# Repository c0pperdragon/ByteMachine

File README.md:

# ByteMachine

Building an 8-bit computer is not exactly trivial. There are always many components involved which are normally
connected to some common address and data bus with complex control signal timings for RAM, ROM and IO controller parts and
whatnot.

One common way for a hobbyist user to actually build such a contraption is using a pre-engineered PCB on which to 
solder all necessary parts. While this can be great fun in itself, it does not teach you much about the hardware 
beyond basic soldering skills. 

Another way is creating the whole computer totally on breadboards. There are great resources and instructions available for
this and it may actually give you the best learning experience. On the other hand, creating a huge breadboard circuit comes with
its own troubles. The cables will often become a total mess, you easily disturb the wrong wires while changing anything, some wires
may make bad contact and you may not get the machine to run at a higher system clock.

With this design as a building block, I wanted to provide some kind of middle ground. The PCB provides the circuity for the system bus, RAM, ROM, clock, powerup reset 
and rudimentary IO. You then need to add a relatively small circuit for the CPU board, depending on the type of CPU to use. This can
be easily done with a single breadboard and a series of jumper links connecting this with the main board. In my experients this creates a 
pretty reliable setup which is even able to use clock frequencies of up to 16Mhz (for the 65Cxx types of CPUs).
Currently I have built and tested setups for the following CPUs:
* [65C02](65c02)
* [65C816](65c816)
* [Z84C00](z84c00)
* [i8088](i8088)

User [oe7twj](https://github.com/oe7twj) has provided me with all documention for this own setup:
* [6809](6809)

## CPU board connector

The main board has a 34 pin single-row connector that carries power and all signals necessary for the CPU to send and receive:
* Power connectors GND and +5V
* CPU Clock 
* Reset (active low)
* WR (active low)
* RD (active low)
* ROM selector 
* 19 Address bus lines
* 8 Data bus lines (bidirectional)

## Clock generator

The main board provides a simple circuit to create a clock signal using a quartz crystal. The quartz itself is socketed, so
you can easily exchange it to experiment with different frequencies. In my tests, this circuit runs reliably with frequencies
from 8Mhz up to 20Mhz (but this may be too fast for your CPU).

## Power-on reset

Most (probably all) supported CPUs need some external help to cleanly start upon power-up. The power-up reset line provides a
low level signal for the first few milliseconds after power is available. 

## Reading and writing strobes

Beyond providing the CPU clock, the main board itself does not use this clock for anything itself, and all accesses to
both RAM, ROM and IO are triggered by asynchronous signals. 

When the CPU needs to do a read, it sets up the address lines as 
well as the ROM selector and then pulls the RD line low. As long as this is in its low state, the board will provide
the requested data on the data bus. It is in the responsibility of the CPU to never drive the data bus itself as long as
the RD line is low.

For writing data to the board, the CPU needs to provide both the address (and ROM selector) and the data on the data bus.
Then it needs to pull WR low and set it high again (after some minimum setup-time). The data that is present at the rising 
edge will be written to the RAM (or IO).

## ROM, RAM, IO

The main board contains 512K of RAM, 512K of ROM (actually a NAND-Flash IC in a ZIF socket for ease of re-programming)
and two 74-series logic ICs to drive the input and output interface.

Contrary to most 8-bit computer designs, there is no dedicated address space to access IO (memory mapped IO) as this would
require some complex address decoding logic. Also a dedicated IO space would reduce the address space available, and for 
a CPU with only 16 address lines total, this is a serious drawback.

In my solution, the only IO the CPU can do is to write into an 8-bit output port register and to read 8 bits from an input 
port. Writing to the output is simply done by writing anywhere to the ROM address range. The data byte written will be stored
in the output register and will show up as voltages on the output port and will also directly drive the output LEDs.
To also allow input with as little logic parts as possible, I chose the following mechanism: 
After a write to the ROM area (and in consequence to the output port as well), the main board switches to "IO mode".
In IO mode, all reads from the RAM area will instead read data form the input port. 
To switch back to normal mode, the CPU needs to do a write to any RAM address. 
Using this scheme, the full range of ROM and RAM is available, as well as 8 output lines and 8 input lines.

## Attaching IO 

With a total of 8 output lines and 8 input lines (each with 10K pullups), basically any kind of serial IO protocol can be implemented
by the CPU: SPI, I2C, UART.

To keep things simple, the ByteBoard does not directly support any kind of IO interrupt line. Therefore basically only IO 
schemes are possible where the CPU is the master of the timing. This is already an inherent characteristic of the I2C and SPI
bus. To implement reliable UART communication, the connected device must support hardware flow control (RTS/CTS) at least 
on the incomming signal, so the CPU needs only to listen for data when it is itself prepared for that.

## Bidirectional lines for I2C 

To form the bi-directional line that is needed for I2C, one output and one input line can be combined.
The output pin can for example drive an open-collector circuit (an IC or only a simple transistor circuit). An even 
simpler possibility is just a diode that pulls down the line when the output pin is driven low, but lets the line
float when the pin is driven high. Due to the pullup resitors already present at the input port pins, this is
basically all that is needed.

## Reprogamming the Flash

From the perspective of the ByteMachine, its ROM is truly read-only. So you need an external programming device
to get new content onto the NAND-Flash. I am using an TL866II+ device which works absolutely fine for me. But 
any other compatible programmer will work, and you can even create an Arduino-Based circuit for that.

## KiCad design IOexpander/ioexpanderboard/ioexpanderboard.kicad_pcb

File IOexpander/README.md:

# IO expander

To allow more sophisticated communication with the outside world than just blinking lights and buttons, 
a small IO board can be attached to the headers of the IO area. This boards provides two serial communication
ports and one SDcard socket.

## Serial ports

Using 4 output pins and 4 input pins, 2 independent serial ports (DSUB-8 connectors) can be
controlled. Because the system architecture of the ByteMachine does not support interrupts,
the CPU will periodically poll the incomming data. This is made possible by the hardware 
handshake with RTS/CTS lines which allows the communication partner to only send data while the 
CPU is actively listening.

## SD card interface

With 3 output pins and 3 input pins, the SD card socket can be driven and there are even
connections to check for the presence of an SD card and for the write-protection switch as well.
Voltage level shifters are used to translate the 5V of the main board to the 3.3V necessary for 
interfacing the SD card itself.

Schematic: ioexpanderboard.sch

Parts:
C1: 100nF; C_0805_2012Metric_Pad1.15x1.40mm_HandSolder
C2: 10uF; C_0805_2012Metric_Pad1.15x1.40mm_HandSolder
JINPUT1: Conn_01x08_Male; PinHeader_1x08_P2.54mm_Vertical
JOUTPUT1: Conn_01x08_Male; PinHeader_1x08_P2.54mm_Vertical
JPOWER1: Conn_01x04_Male; PinHeader_1x04_P2.54mm_Vertical
JSERIAL1, JSERIAL2: DB9_Male; DSUB-9_Male_Horizontal_P2.77x2.54mm_EdgePinOffset9.40mm
R1, R2, R3, R4: 330; R_0805_2012Metric_Pad1.15x1.40mm_HandSolder
SDCard1: SD_Card; sdcardsocket
U1: 74LVC86; SOIC-14_3.9x8.7mm_P1.27mm
U2: LD1117S33TR_SOT223; SOT-223-3_TabPin2

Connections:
+3V3: C1.1, C2.1, SDCard1.4, U1.14 (VCC), U2.2 (VO)
+5V: JPOWER1.4, U2.3 (VI)
/CARD_DETECT: JINPUT1.8, SDCard1.10
/CS: JOUTPUT1.2, U1.2
/CTS1: JINPUT1.2, R2.2
/CTS2: JINPUT1.4, R4.2
/MISO: JINPUT1.6, U1.8
/MOSI: JOUTPUT1.1, U1.4
/RTS1: JOUTPUT1.6, JSERIAL1.9
/RTS2: JOUTPUT1.8, JSERIAL2.9
/RXD1: JINPUT1.1, R1.2
/RXD2: JINPUT1.3, R3.2
/SCK: JOUTPUT1.3, U1.13
/TXD1: JOUTPUT1.5, JSERIAL1.3
/TXD2: JOUTPUT1.7, JSERIAL2.3
/WRITE_PROTECT: JINPUT1.7, SDCard1.11
GND: C1.2, C2.2, JINPUT1.5, JPOWER1.2, JPOWER1.3, JSERIAL1.5, JSERIAL2.5, SDCard1.3, SDCard1.6, SDCard1.12, SDCard1.13, U1.1, U1.5, U1.7 (GND), U1.9, U1.12, U2.1 (GND)
unnamed: JSERIAL1.2, R2.1
unnamed: JSERIAL1.8, R1.1
unnamed: JSERIAL2.2, R4.1
unnamed: JSERIAL2.8, R3.1
unnamed: SDCard1.1, U1.3
unnamed: SDCard1.2, U1.6
unnamed: SDCard1.5, U1.11
unnamed: SDCard1.7, U1.10

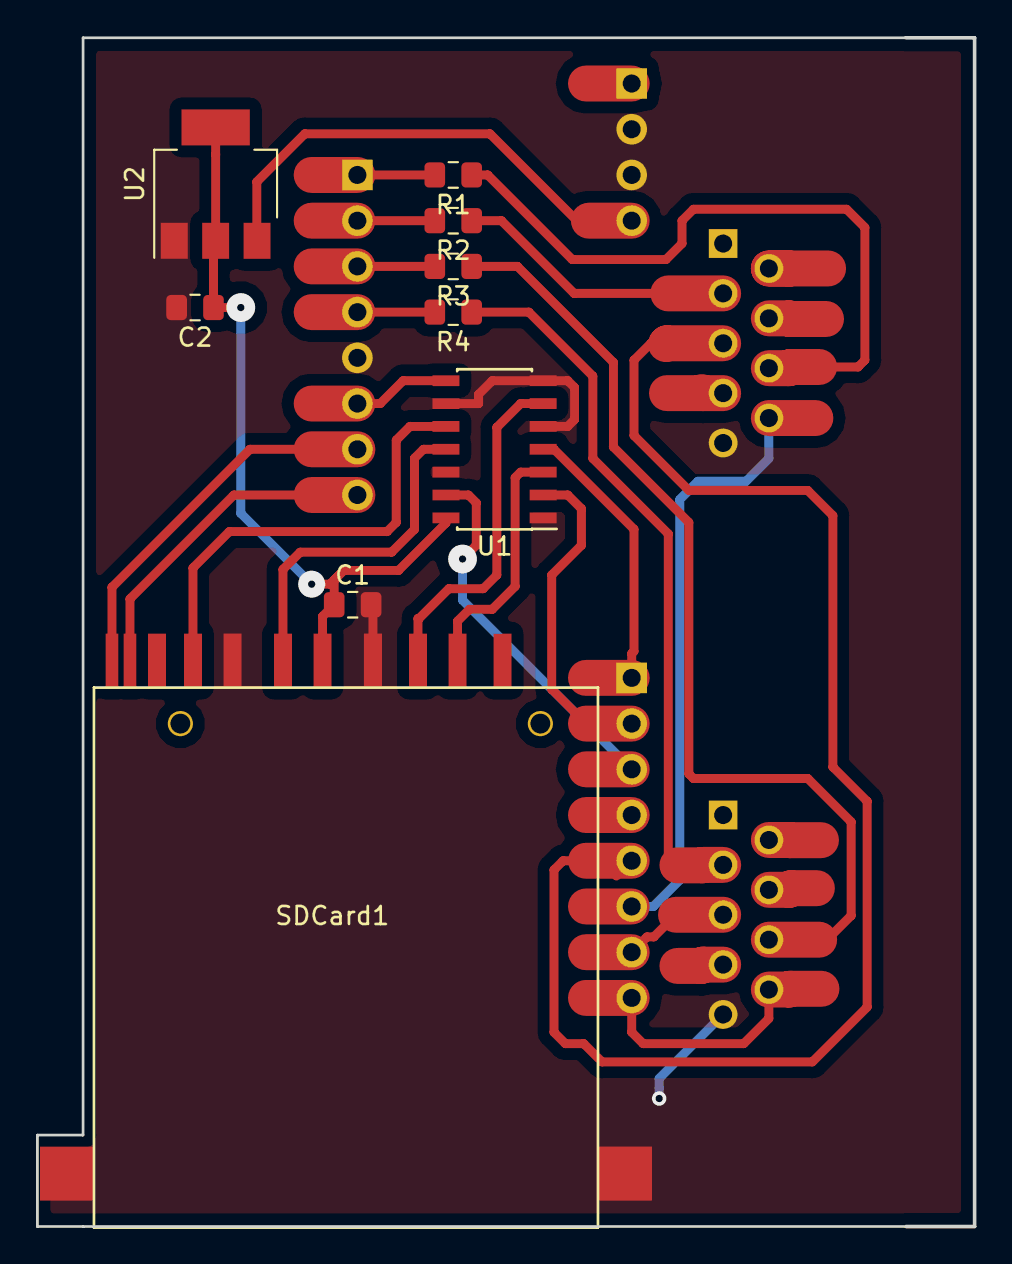
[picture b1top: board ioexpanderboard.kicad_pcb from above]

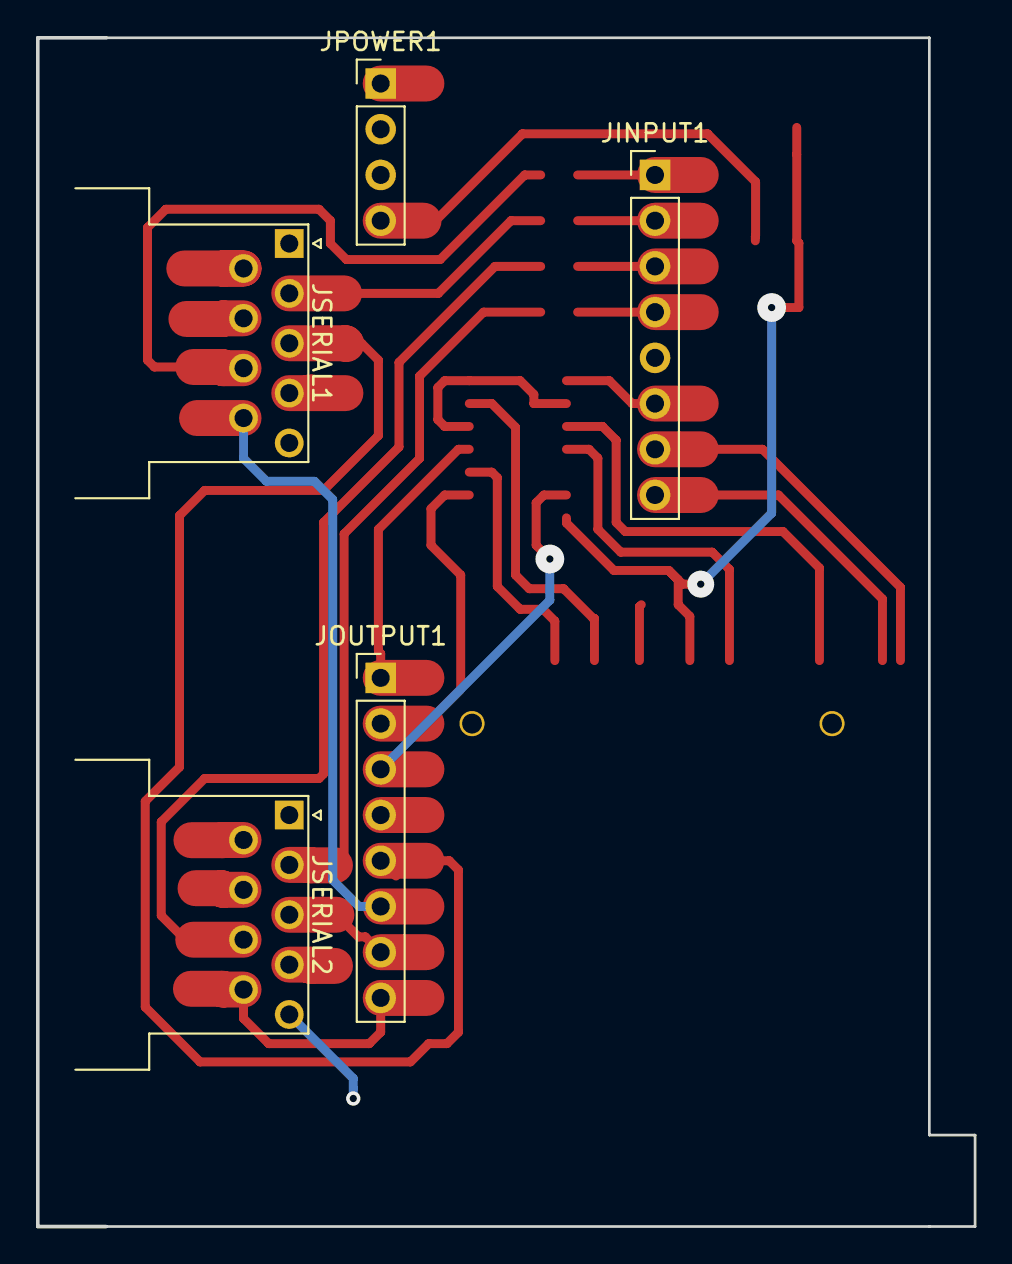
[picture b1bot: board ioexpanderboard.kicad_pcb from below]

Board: 2 copper layers, 52.0 x 66.0 mm, 14 parts (5 on the bottom side), 25 nets.

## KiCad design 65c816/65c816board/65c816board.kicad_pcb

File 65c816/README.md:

# 65c816

This not so well known CPU is an extended variant of the 6502. It extends the address space to 24 bit
and some internal registers can be used with a width of 16 bit.
It was used in the Super Nintendo Entertainment System (SNES) as well as the Apple IIGS, but it was never
very accessible to hobby programmers back in the day. Even for todays hardware DIY fans this CPU 
is quite tricky to use because of its multiplexed data bus and other details.

## Theory of operation

The main problem when using this CPU is the way in which the high address lines are multiplexed on the data lines.
With the use of a latch and two more 74-series logic parts (one quad NAND and one quad OR), this can be solved.
Generation of RD and WR signals is done in the same way as on the 65C02 board. To avoid bus collisions during the
first half of each cycle as much as possible, the CPU is driven with a slightly delayed clock so the time spans where the 
CPU writes the higher address lines to the data bus do least overlap with the time spans when the memory writes 
back the data. With this simple circuit, collisions can not be entirely avoided, but it seems to be OK
to have collisions for only a few nanoseconds on each clock cycle.

The schematic diagram (65c816board.pdf) is designed to directly show the breadboard layout. The connections of some bus lines 
are only shown by their designators to avoid too much clutter in the diagram.

## Memory map

The 16M address space which the 65c816 can access is larger than the total available RAM and ROM space of the 
main board, so many addresses map to the same target locations. 
After reset (in "emulation mode"), the CPU is reading the reset vector from bank 0 and the startup code also can only be located in this bank. 
But in normal operation it would be beneficial to have the whole bank 0 available for RAM.
Therefore the board uses the "emulation" output pin to provide two different memory mappings. One solely for 
the purpose of bringing the CPU up into native mode. In this emulation mode, all addresses only  map
to the ROM and not much meaningful work can be done (except switching to native mode).

Memory map

| CPU address    | type   | mem address  |
| -------------- | -------| -------------|
| 000000..07FFFF | RAM(*) | 00000..7FFFF |
| 800000..87FFFF | ROM    | 00000..7FFFF |

(*) In emulation mode this memory range also maps to ROM.

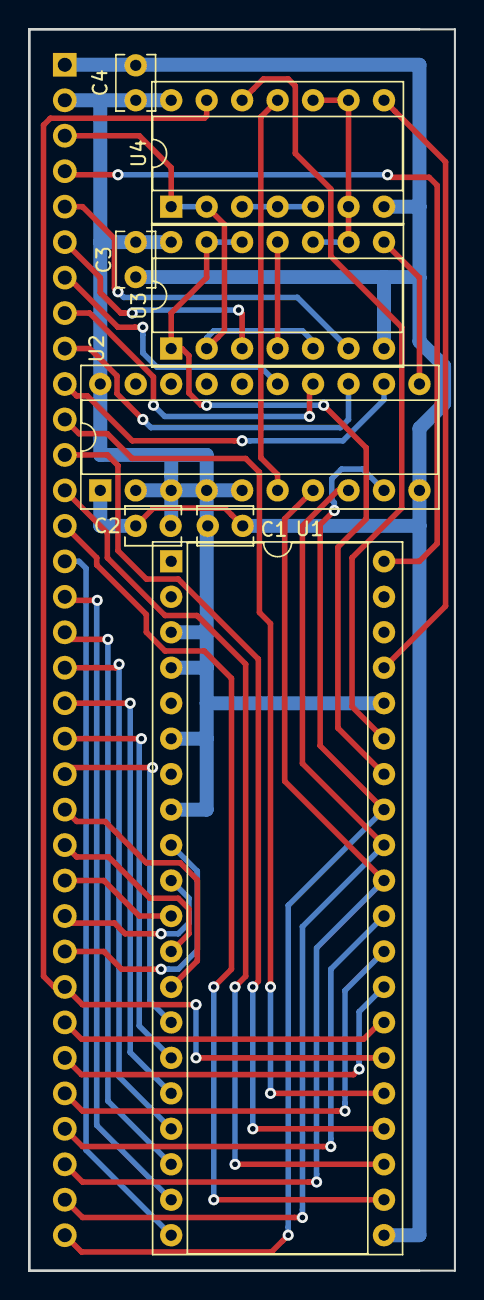
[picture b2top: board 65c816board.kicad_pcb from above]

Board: 2 copper layers, 30.5 x 88.9 mm, 9 parts (1 on the bottom side), 42 nets.

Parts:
C1, C2, C3, C4: 100nF; C_Disc_D3.8mm_W2.6mm_P2.50mm
J1: Conn_01x34_Male; PinHeader_1x34_P2.54mm_Vertical
U1: w65c816; DIP-40_W15.24mm_Socket
U2: 74AC573; DIP-20_W7.62mm_Socket
U3: 74AC00; DIP-14_W7.62mm_Socket
U4: 74AC32; DIP-14_W7.62mm_Socket

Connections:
/5V: C1.2, C2.2, C3.1, C4.1, J1.2, U1.3, U1.4, U1.6, U1.8, U1.36, U2.2, U2.3, U2.4, U2.5, U2.20, U3.14, U4.14
/A0: J1.26, U1.9
/A1: J1.25, U1.10
/A2: J1.24, U1.11
/A3: J1.23, U1.12
/A4: J1.22, U1.13
/A5: J1.21, U1.14
/A6: J1.20, U1.15
/A7: J1.19, U1.16
/A8: J1.18, U1.17
/A9: J1.17, U1.18
/A10: J1.16, U1.19
/A11: J1.15, U1.20
/A12: J1.14, U1.22
/A13: J1.13, U1.23
/A14: J1.12, U1.24
/A15: J1.11, U1.25
/A16: J1.10, U2.12
/A17: J1.9, U2.13
/A18: J1.8, U2.14
/CLK: J1.3, U3.2, U3.5, U4.1, U4.2
/D0: J1.34, U1.33, U2.9
/D1: J1.33, U1.32, U2.8
/D2: J1.32, U1.31, U2.7
/D3: J1.31, U1.30
/D4: J1.30, U1.29
/D5: J1.29, U1.28
/D6: J1.28, U1.27
/D7: J1.27, U1.26, U4.13
/GND: C1.1, C2.1, C3.2, C4.2, J1.1, U1.21, U2.1, U2.10, U3.7, U4.7
/RD#: J1.6, U3.3
/RES#: J1.4, U1.40
/ROM: J1.7, U2.15
/WR#: J1.5, U3.6
unnamed: U1.34, U3.1, U3.12, U3.13
unnamed: U1.35, U4.12
unnamed: U1.37, U4.8
unnamed: U2.6, U4.11
unnamed: U2.11, U3.8
unnamed: U3.9, U3.10, U4.6, U4.9, U4.10
unnamed: U3.4, U3.11
unnamed: U4.3, U4.4, U4.5

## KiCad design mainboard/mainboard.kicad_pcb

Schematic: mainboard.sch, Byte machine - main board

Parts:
C1, C6, C7, C8, C9, C10, C11, C13: 100nF; C_Disc_D3.8mm_W2.6mm_P2.50mm
C2: 470uF; CP_Radial_D8.0mm_P5.00mm
C3, C5: 33pF; C_Disc_D5.0mm_W2.5mm_P5.00mm
C4: 10uF; C_Disc_D5.0mm_W2.5mm_P5.00mm
D0, D1, D2, D3, D4, D5, D6, D7, D9: LED_Small; LED_D3.0mm
JBUS1: Conn_01x34_Female; PinSocket_1x34_P2.54mm_Vertical
JIN1: Conn_01x08_Male; PinHeader_1x08_P2.54mm_Vertical
JOUT1: Conn_01x08_Male; PinHeader_1x08_P2.54mm_Vertical
JPOWER1: Barrel_Jack_Switch; BarrelJack_Horizontal
JPOWER2: Conn_01x04_Male; PinHeader_1x04_P2.54mm_Vertical
R1: 220k; R_Axial_DIN0207_L6.3mm_D2.5mm_P7.62mm_Horizontal
R2: 22; R_Axial_DIN0207_L6.3mm_D2.5mm_P7.62mm_Horizontal
R3: 1M; R_Axial_DIN0207_L6.3mm_D2.5mm_P7.62mm_Horizontal
R4: 1k; R_Axial_DIN0207_L6.3mm_D2.5mm_P7.62mm_Horizontal
RN1: 10k; R_Array_SIP9
RN4: 1k; R_Array_SIP9
SW1: SW_DPDT_x2; SW_CuK_JS202011CQN_DPDT_Straight
U1: 74HC04; DIP-14_W7.62mm_Socket
U2: AS6C4008; DIP-32_W15.24mm_Socket
U3: 74AC32; DIP-14_W7.62mm_Socket
U4: 74AC00; DIP-14_W7.62mm_Socket
U5: SST39SF040; DIP-32_W15.24mm_Socket
U6: NE555; DIP-8_W7.62mm
U7: 74HC245; DIP-20_W7.62mm_Socket
U9: 74HC574; DIP-20_W7.62mm_Socket
Y1: Crystal; Crystal_HC18-U_Vertical

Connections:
+5V: C1.2, C2.1, C4.1, C6.2, C8.1, C9.2, C10.1, C11.1, C13.1, JBUS1.2, JPOWER2.4, R3.2, R4.1, RN1.1, SW1.1, SW1.4, U1.14 (VCC), U2.32, U3.14, U4.14 (VCC), U5.31, U5.32, U6.8 (VCC), U7.20 (VCC), U9.20 (VCC)
/A0: JBUS1.26, U2.12, U5.12
/A1: JBUS1.25, U2.11, U5.11
/A2: JBUS1.24, U2.10, U5.10
/A3: JBUS1.23, U2.9, U5.9
/A4: JBUS1.22, U2.8, U5.8
/A5: JBUS1.21, U2.7, U5.7
/A6: JBUS1.20, U2.6, U5.6
/A7: JBUS1.19, U2.5, U5.5
/A8: JBUS1.18, U2.27, U5.27
/A9: JBUS1.17, U2.26, U5.26
/A10: JBUS1.16, U2.23, U5.23
/A11: JBUS1.15, U2.25, U5.25
/A12: JBUS1.14, U2.4, U5.4
/A13: JBUS1.13, U2.28, U5.28
/A14: JBUS1.12, U2.31, U5.29
/A15: JBUS1.11, U2.3, U5.3
/A16: JBUS1.10, U2.2, U5.2
/A17: JBUS1.9, U2.30, U5.30
/A18: JBUS1.8, U2.1, U5.1
/CLK: JBUS1.3, U1.6
/CPOUTPUT: U3.11, U4.1, U9.11 (Cp)
/D0: JBUS1.34, U2.13, U5.13, U7.9 (A7), U9.9 (D7)
/D1: JBUS1.33, U2.14, U5.14, U7.8 (A6), U9.8 (D6)
/D2: JBUS1.32, U2.15, U5.15, U7.7 (A5), U9.7 (D5)
/D3: JBUS1.31, U2.17, U5.17, U7.6 (A4), U9.6 (D4)
/D4: JBUS1.30, U2.18, U5.18, U7.5 (A3), U9.5 (D3)
/D5: JBUS1.29, U2.19, U5.19, U7.4 (A2), U9.4 (D2)
/D6: JBUS1.28, U2.20, U5.20, U7.3 (A1), U9.3 (D1)
/D7: JBUS1.27, U2.21, U5.21, U7.2 (A0), U9.2 (D0)
/IOMODE: U3.2, U4.3, U4.4, U4.12
/OEINPUT: U3.8, U7.19 (CE)
/OERAM: U2.24, U3.3
/OEROM: U3.6, U5.24
/RAM: U1.10, U3.5, U3.13, U4.5, U4.10
/RD#: JBUS1.6, U3.1, U3.4, U3.10
/RES#: JBUS1.4, U1.8
/RESETIO: U4.8, U4.13
/ROM: JBUS1.7, U1.11, U2.22
/VIN: JPOWER1.1, JPOWER2.1, SW1.2, SW1.5
/WR#: JBUS1.5, U1.13, U2.29, U3.12
GND: C1.1, C2.2, C3.2, C4.2, C5.2, C6.1, C7.2, C8.2, C9.1, C10.2, C11.2, C13.2, D9.1, JBUS1.1, JPOWER1.2, JPOWER1.3, JPOWER2.2, JPOWER2.3, RN4.1, U1.7 (GND), U2.16, U3.7, U4.7 (GND), U5.16, U5.22, U6.1 (GND), U7.1 (A->B), U7.10 (GND), U9.1 (OE), U9.10 (GND)
unnamed: C3.1, R1.2, U1.1, Y1.1
unnamed: C5.1, R2.2, Y1.2
unnamed: C7.1, R3.1, U6.2 (TR), U6.6 (THR)
unnamed: D0.1, RN4.2
unnamed: D0.2, JOUT1.8, U9.12 (Q7)
unnamed: D1.1, RN4.3
unnamed: D1.2, JOUT1.7, U9.13 (Q6)
unnamed: D2.1, RN4.4
unnamed: D2.2, JOUT1.6, U9.14 (Q5)
unnamed: D3.1, RN4.5
unnamed: D3.2, JOUT1.5, U9.15 (Q4)
unnamed: D4.1, RN4.6
unnamed: D4.2, JOUT1.4, U9.16 (Q3)
unnamed: D5.1, RN4.7
unnamed: D5.2, JOUT1.3, U9.17 (Q2)
unnamed: D6.1, RN4.8
unnamed: D6.2, JOUT1.2, U9.18 (Q1)
unnamed: D7.1, RN4.9
unnamed: D7.2, JOUT1.1, U9.19 (Q0)
unnamed: D9.2, R4.2
unnamed: JIN1.1, RN1.2, U7.18 (B0)
unnamed: JIN1.2, RN1.3, U7.17 (B1)
unnamed: JIN1.3, RN1.4, U7.16 (B2)
unnamed: JIN1.4, RN1.5, U7.15 (B3)
unnamed: JIN1.5, RN1.6, U7.14 (B4)
unnamed: JIN1.6, RN1.7, U7.13 (B5)
unnamed: JIN1.7, RN1.8, U7.12 (B6)
unnamed: JIN1.8, RN1.9, U7.11 (B7)
unnamed: R1.1, R2.1, U1.2, U1.3
unnamed: U1.4, U1.5
unnamed: U1.9, U6.3 (Q)
unnamed: U1.12, U4.9
unnamed: U3.9, U4.6
unnamed: U4.2, U4.11

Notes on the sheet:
RAM
ROM
INPUT
OUTPUT
MODE REGISTER
CLOCK
POWER-ON RESET

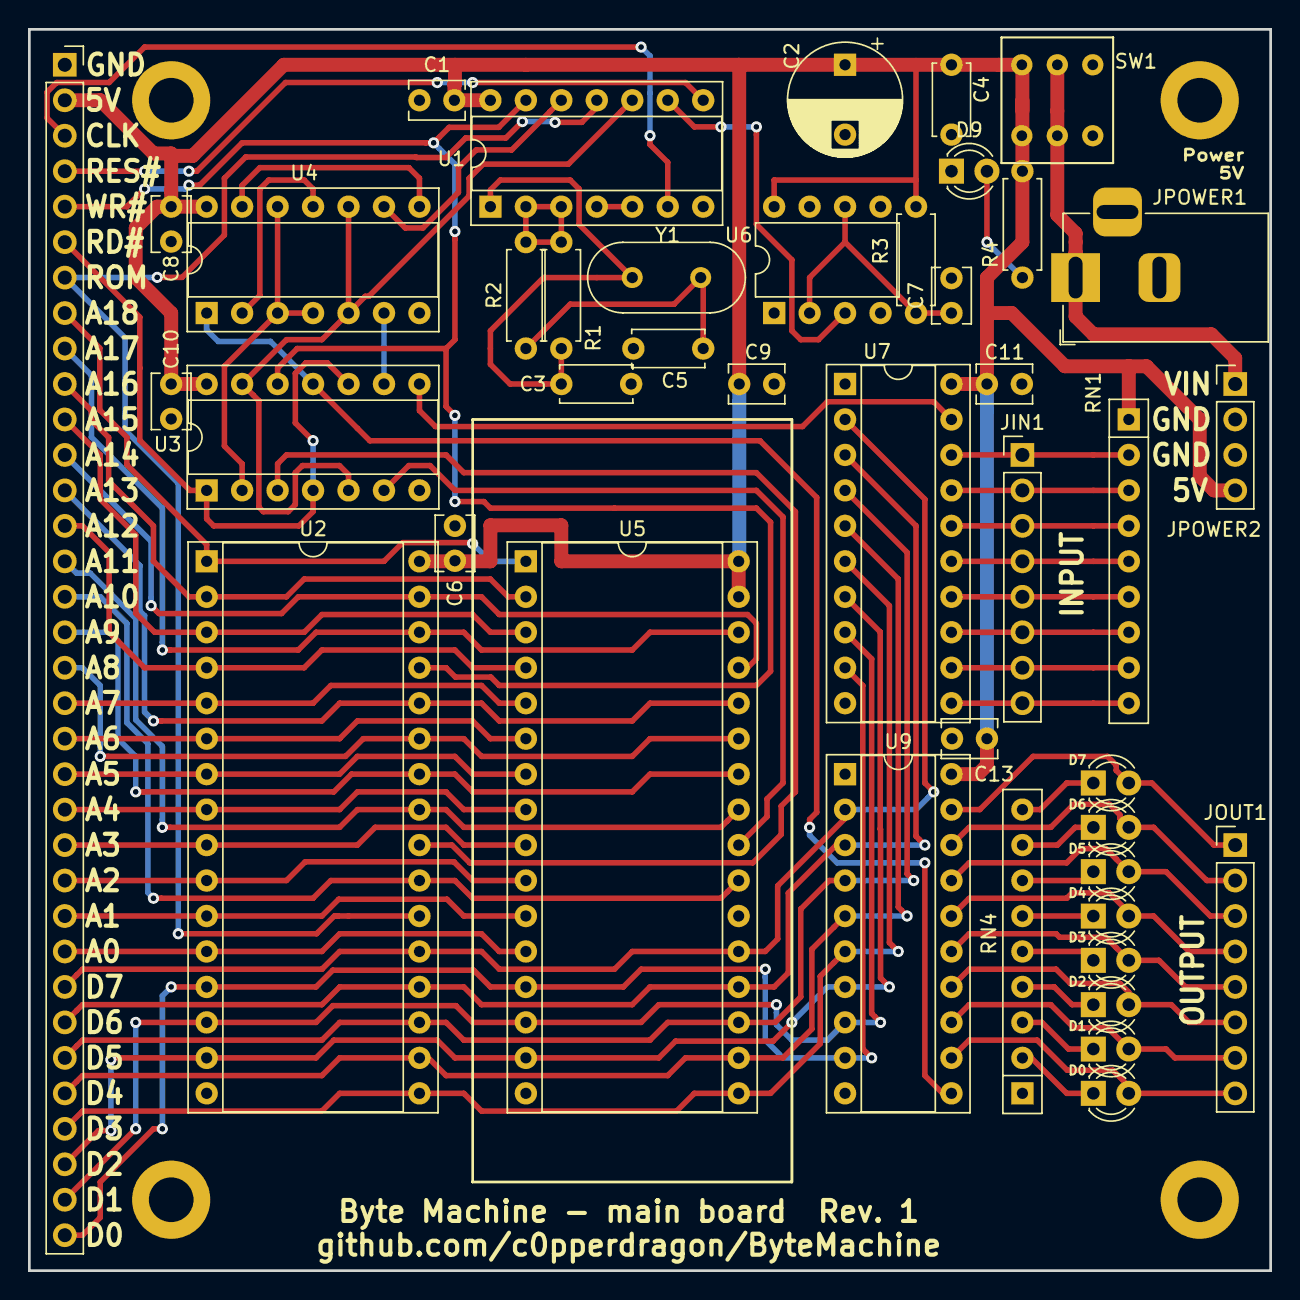
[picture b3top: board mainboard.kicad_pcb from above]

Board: 2 copper layers, 88.9 x 88.9 mm, 42 parts (0 on the bottom side), 76 nets.

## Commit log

2015-09-04 First program structure for the ByteMachine.
2015-09-11 Working CPU. "Hello World!" sample running.
2015-09-11 Assembler for ByteMachine code
2015-09-11 Changed instruction set (only in spec)
2015-09-15 Simplified structure
    ByteMachine now uses one entity. On board design file, it is integrated
    with ram and io-blocks.
2015-09-16 Wishbone support
2015-09-17 Implemented VM in java, changed memory model
    The ByteMachine now has a Harvard Architecture and a unified stack for
    operands and return addresses
2015-09-21 Redesign von instruction set
    I have complete reworked the instruction set of the ByteMachine. It is
    now reduced to a bare minimum with still being usable. As a proof of
    concept, I have implemented a MD5 checksum calculator which runs in my
    new ByteMachine VM.
    I think with this new architecture the consumption of LUTs in an FPGA
    should be quite low,, using ram blocks even for the operand stack and
2015-09-23 More instruction set tweaks, Ultra-minimal CPU.
    I have decided to put the whole operand stack into a synchronous RAM (8
    MLABs on an Cyclone V) and use only the barest minimum of registers.
    Together with a mimimum ALU, This should lead to an extremly small
    footprint while still maintaining a reasonable speed.
2015-09-29 Re-designed core: Use 1KB RAM for everything
    The new solution puts the whole operand stack,, the address stack and
    the indexable memory into a single 1 KByte memory.
    The instructions are fetched from a ROM of up to 4 KBytes.
2017-02-05 commite last change made by IDE
2017-04-13 Start to completely redesign the instruction set to have a true single-byte instructions in all cases that can always be executed in a single clock.
2017-04-14 Ongoing development
    Assembler and virtual machine for die new ByteMachine
2017-04-26 Changes in instruction set
    I changed the instruction set a bit to make it possible to implement the
    machine with a synchronious ram interface (faster and properly supported
    by altera FPGAs)
2017-05-02 Tweaking instruction set. More work on sample programs.
2017-05-03 Implement proof of concept
    Re-Implement the MD5 algorithm on the current ByteMachine instruction
    set. Very cumbersome, but can be done.
2017-05-12 Implemetation of new version in VHDL
2020-05-26 Designing a generic main board
2020-05-29 Main board layout tweaks
2020-06-01 More PCB design First tiny program running
2020-06-02 Fully working test program
2020-06-04 Repurposing this repo (and product name) for my gernic 8-bit computer main board.
2020-06-05 Reworked schematics for the WD65C02 processor board.
2020-06-07 Redesign port access to use a state flip-flop made of NANDs instead of wasting a bit of the dedicatd output IC.
2020-06-12 Rename A19 to RAM to create two distinct address spaces.
2020-06-12 Tweak schematics to only use one GND and one +5V rail
2020-06-12 Start with 65C816 schematics
2020-06-15 Breadboard layout for the 65C816 CPU board.
2020-06-15 Rework schematics and documentation
2020-06-16 Documentation pictures
2020-06-16 Working setup for the 65c816
2020-06-17 Remove unnecessary pullup at Rdy pin
2020-06-20 Switch meaning of the A19 pin from RAM to ROM. Use pull-ups instead of pull-downs for the input port.
2020-06-22 Docu
2020-06-22 Add power input on pin header to allow USB device to drive the machine.
2020-06-24 Layout for 65C816 CPU board
2020-06-24 Better layout for 65c816 CPU board
2020-06-25 First example programs for the 65C816
2020-06-26 Working example using all features of C mapped to various code and data segments types.
2020-06-27 Implement port read function
2020-06-27 Remove protection resistors for input port. Stagger ports so an IO board will have better mechanical stability
2020-06-28 Schematic and test program for the Z84C00 processor
2020-06-28 Image of Z80 assembly
2020-06-28 Finshed layout for manifacture
2020-06-29 Update schematics
2020-07-08 Restructure memory ROM map Make dedicated bit-setter and bit-clearer methods for the port pins
2020-07-08 Calibrate libraries to assume a 12Mhz clock
2020-07-08 UART send facility
2020-07-09 Bidirectional uart communication
2020-08-21 Modify memory map for the 65c02 to allow the P8088 to use the common rom image for simple test program without clashing.
2020-08-21 Change mainboard to have larger holes for the ZIF socket and the power switch.
2020-08-22 Start with the i8088 board
2020-09-03 Circuit and test program for the Intel 8088
2020-09-03 Add i8088 to the list
2020-09-03 Add picture
2020-09-06 Design IO expander board and start programming
2020-10-05 Redefine ByteCPU to implement it in 7400 logic. Prototype of assembler.
2020-10-06 Intel hex format output from byte assembler
2020-10-09 Complete schematics for the ByteCPU
2020-10-10 Fix mistake in SELPC signal generation. More docu.
2020-10-10 Share logic ICs between control and addressing to save 2 parts.
2020-10-12 Ongoing development UART bridge
2020-10-13 Working version of SPI-to-UART bridge.
2020-10-19 Re-arrange the interconnect to better match the pin layout of the various chips.
2020-10-21 Modifications to fit the wiring to the physical layout of the 7400 logic. Bugfix: RD line was active during JMP instruction.
2020-10-21 Fixed assembler bug and bug in ledanimation program.
2020-10-23 Rework control logic to allow and additional IO instruction
2020-10-25 Rework all opcodes to speed up the decoding stage by 10 ns
2020-10-26 Small fixes after rework
2020-10-26 Split off the breadbin to a different project.
2021-04-02 Production files for cpu board. More work on IO expander board
2021-04-02 Typo
2021-04-12 Remove reference to the discontinued breadbin cpu
2021-04-14 Prepare test program to run on the BreadBin
2021-04-24 Transfer OS816 into its own repo.
2022-05-14 6809 CPU
